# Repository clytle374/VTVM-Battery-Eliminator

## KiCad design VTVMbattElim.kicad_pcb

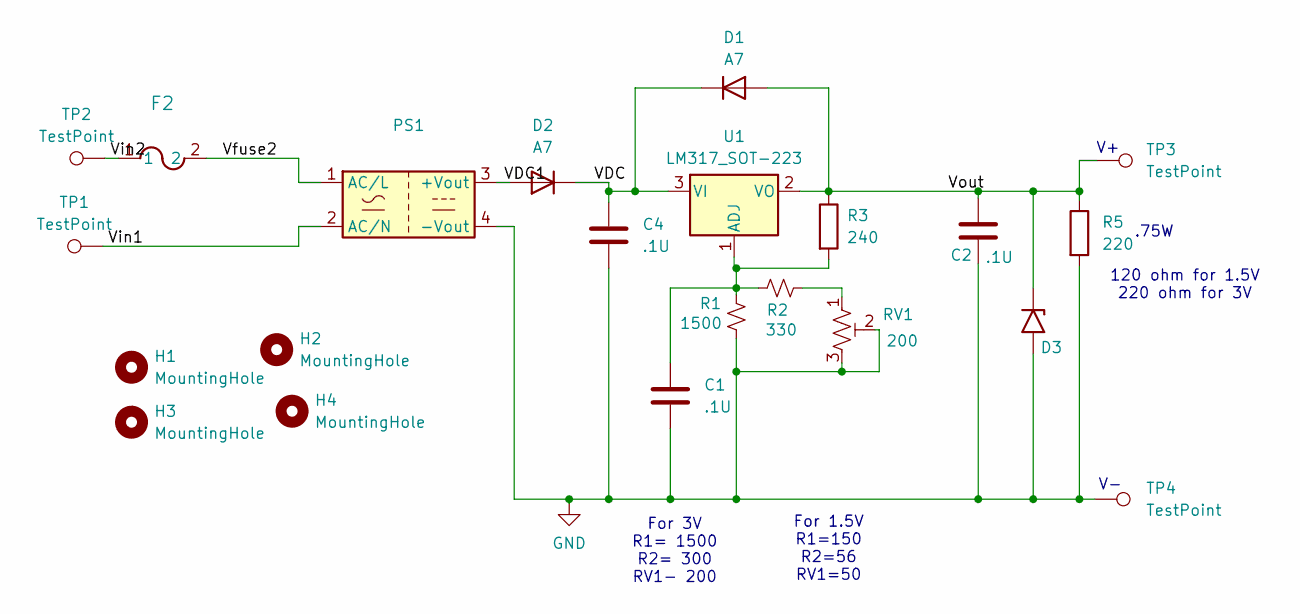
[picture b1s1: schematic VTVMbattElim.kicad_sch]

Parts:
C1, C2, C4: .1U; C_1206_3216Metric_Pad1.33x1.80mm_HandSolder
D1, D2: A7; D_SOD-123F-HandSolder
D3: SMAJ6.5A-13-F; D_SMA-SMB_Universal_Handsoldering
F2: 0034.6000; Fuse_Schurter_UMT250
H1, H2, H3, H4: MountingHole; MountingHole_3.2mm_M3
PS1: ZPI03S0600WC
R1: 1500; R_1206_3216Metric_Pad1.30x1.75mm_HandSolder
R2: 330; R_1206_3216Metric_Pad1.30x1.75mm_HandSolder
R3: 240; R_1206_3216Metric_Pad1.30x1.75mm_HandSolder
R5: 220; R_1206_3216Metric_Pad1.30x1.75mm_HandSolder
RV1: 200; Potentiometer_Bourns_3296W_Vertical
TP1, TP2, TP3, TP4: TestPoint; Pin_D1.4mm_L8.5mm_W2.8mm_FlatFork
U1: LM317_SOT-223; SOT-223-3_TabPin2

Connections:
/VDC: C4.1, D1.1 (K), D2.1 (K), U1.3 (VI)
/VDC1: D2.2 (A), PS1.3 (+Vout)
/Vfuse2: F2.2, PS1.1 (AC/L)
/Vin1: PS1.2 (AC/N), TP1.1
/Vin2: F2.1, TP2.1
/Vout: C2.1, D1.2 (A), D3.1 (A1), R3.1, R5.1, TP3.1, U1.2 (VO)
GND: C1.2, C2.2, C4.2, D3.2 (A2), PS1.4 (-Vout), R1.2, R5.2, RV1.2, RV1.3, TP4.1
unnamed: R2.2, RV1.1
unnamed: C1.1, R1.1, R2.1, R3.2, U1.1 (ADJ)

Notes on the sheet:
.75W
120 ohm for 1.5V 220 ohm for 3V
For 1.5V R1=150 R2=56 RV1=50
For 3V R1= 1500 R2= 300 RV1- 200

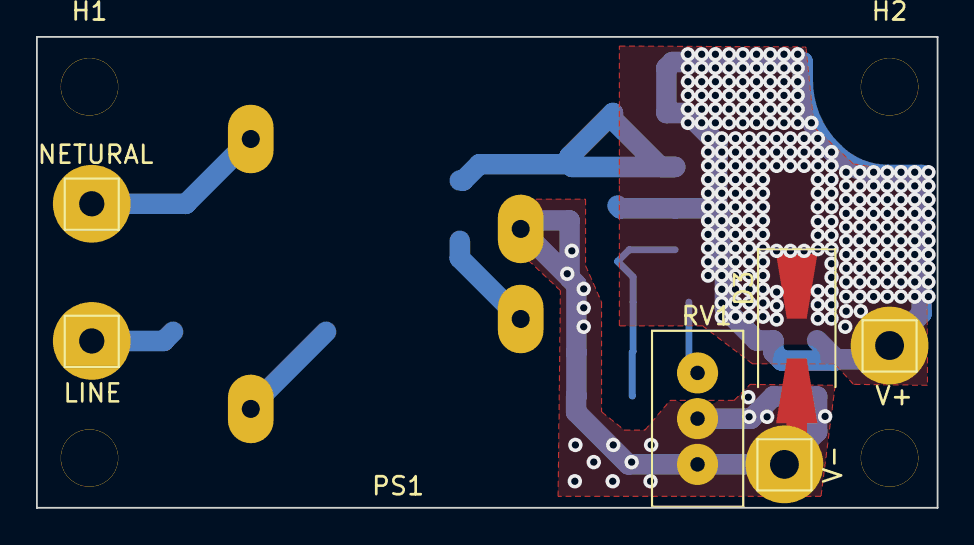
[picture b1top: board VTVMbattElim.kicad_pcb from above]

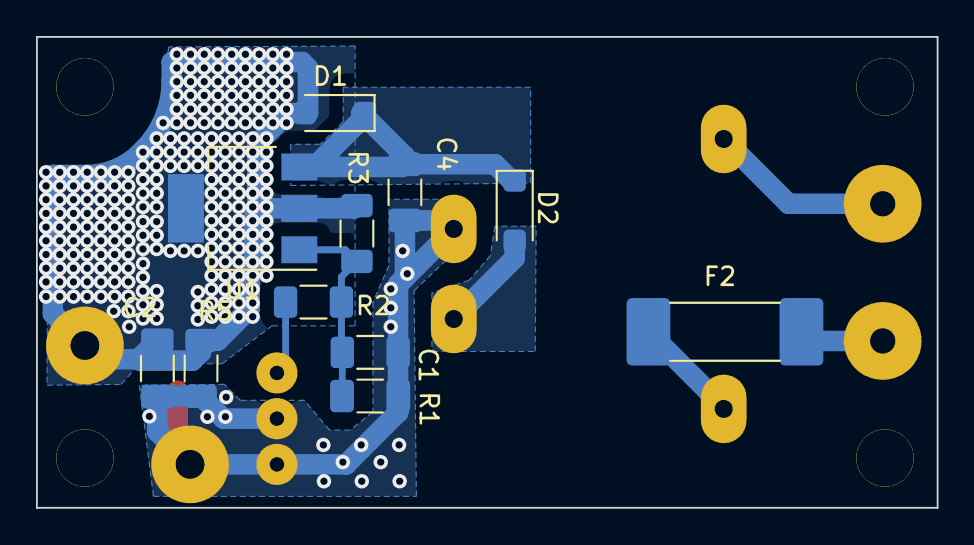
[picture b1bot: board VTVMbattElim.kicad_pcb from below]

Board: 2 copper layers, 50.0 x 26.2 mm, 22 parts (11 on the bottom side), 9 nets.

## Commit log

2024-07-20 inital commit
2024-10-11 cleanup
